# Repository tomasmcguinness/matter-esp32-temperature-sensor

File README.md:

# matter-esp32-temperature-sensor
A simple Matter enabled NTC temperature sensor for ESP32

> [!CAUTION]
> The PCB design has some issues that need to be resolved.

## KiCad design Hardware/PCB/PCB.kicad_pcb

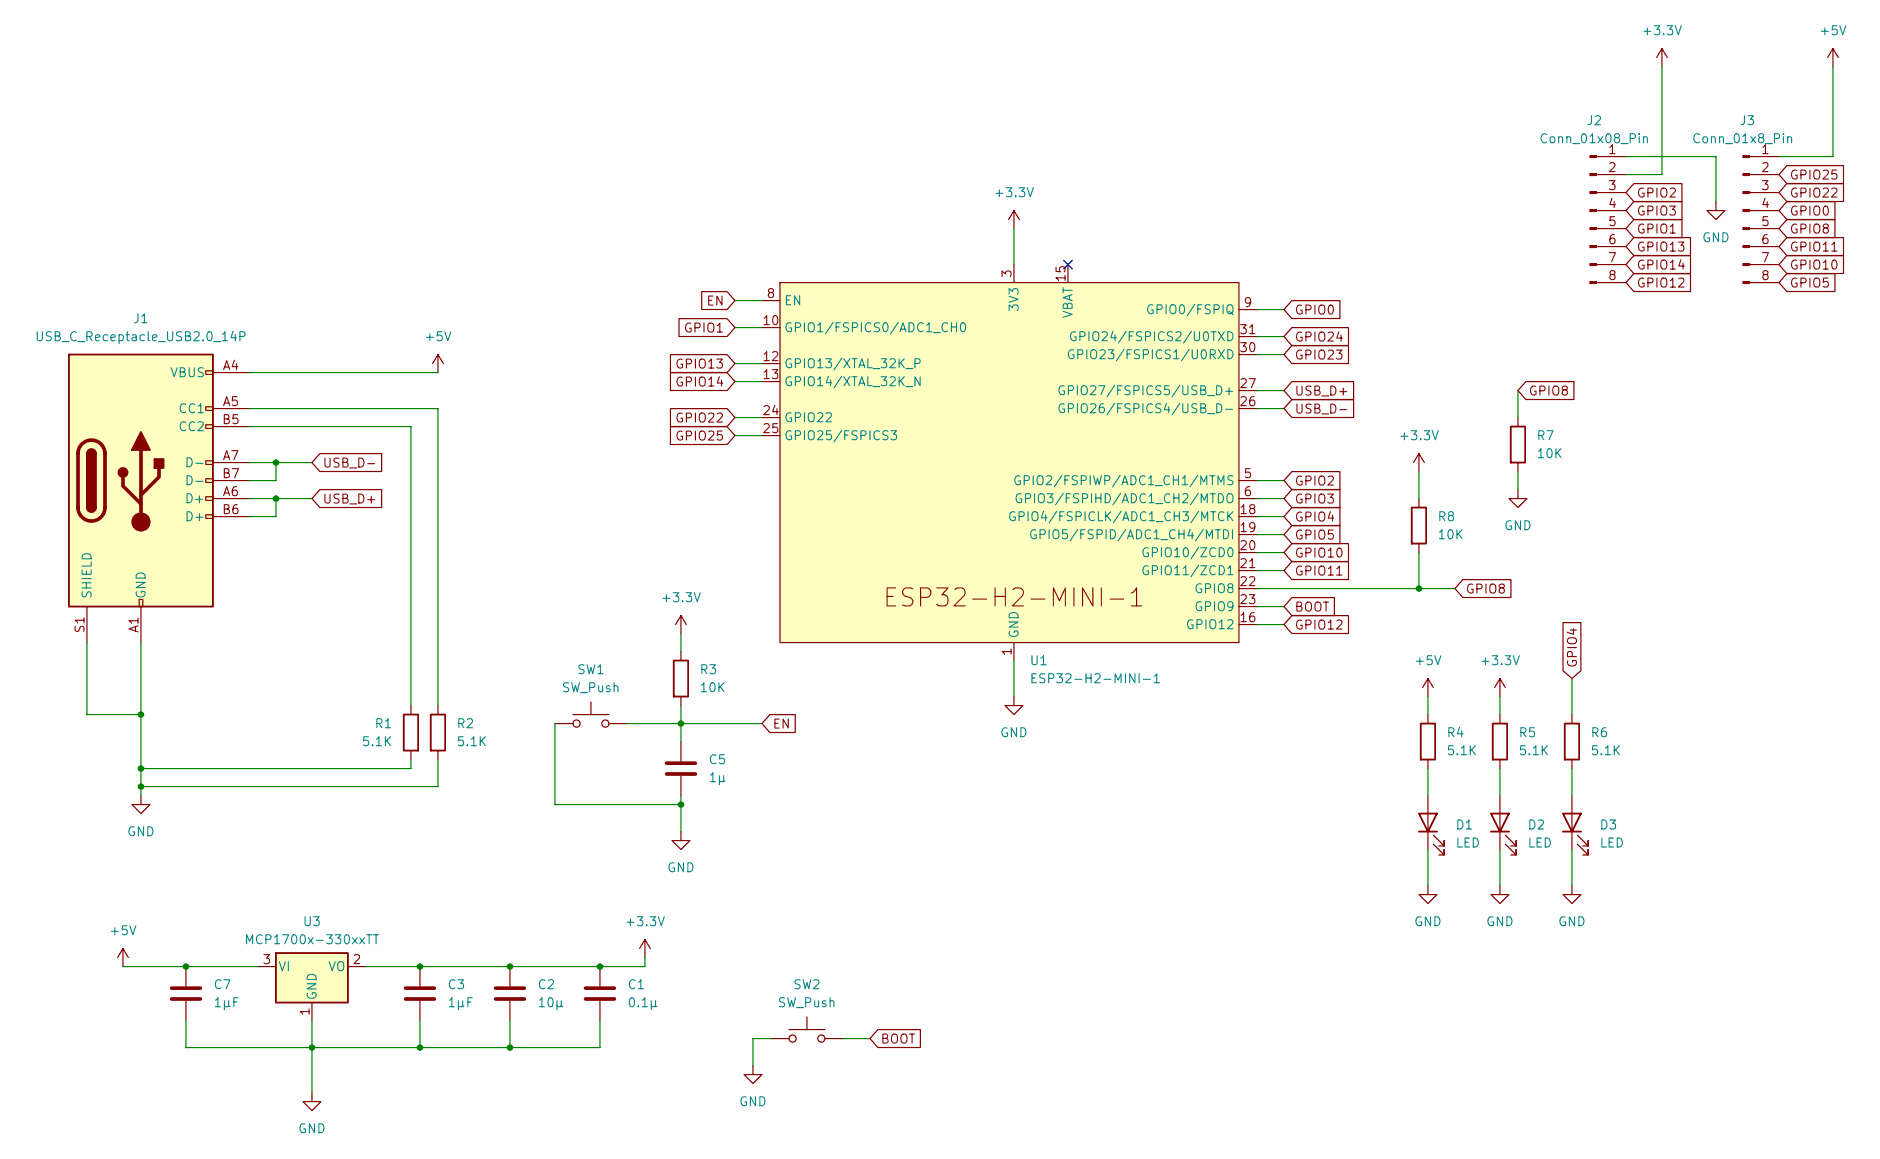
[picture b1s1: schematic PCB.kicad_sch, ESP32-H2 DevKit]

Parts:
C1: 0.1µ; C_0805_2012Metric
C2: 10µ; C_0805_2012Metric
C3, C7: 1µF; C_0805_2012Metric
C5: 1µ; C_0805_2012Metric
D1, D2, D3: LED; LED_0805_2012Metric
J1: USB_C_Receptacle_USB2.0_14P; USB_C_Receptacle_GCT_USB4105-xx-A_16P_TopMnt_Horizontal
J2: Conn_01x08_Pin; PinHeader_1x08_P2.54mm_Vertical
J3: Conn_01x8_Pin; PinHeader_1x08_P2.54mm_Vertical
R1, R2, R4, R5, R6: 5.1K; R_0805_2012Metric
R3, R7, R8: 10K; R_0805_2012Metric
SW1, SW2: SW_Push; SW_SPST_TS-1088-xR025
U1: ESP32-H2-MINI-1
U3: MCP1700x-330xxTT; SOT-23

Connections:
+3.3V: C1.1, C2.1, C3.1, J2.2, R3.1, R5.1, R8.1, U1.3 (3V3), U3.2 (VO)
+5V: C7.1, J1.A4 (VBUS), J1.A9 (VBUS), J1.B4 (VBUS), J1.B9 (VBUS), J3.1, R4.1, U3.3 (VI)
BOOT: SW2.2, U1.23 (GPIO9)
EN: C5.1, R3.2, SW1.2, U1.8 (EN)
GND: C1.2, C2.2, C3.2, C5.2, C7.2, D1.1 (K), D2.1 (K), D3.1 (K), J1.A1 (GND), J1.A12 (GND), J1.B1 (GND), J1.B12 (GND), J1.S1 (SHIELD), J2.1, R1.2, R2.2, R7.2, SW1.1, SW2.1, U1.1 (GND), U1.2 (GND), U1.11 (GND), U1.14 (GND), U1.36 (GND), U1.37 (GND), U1.38 (GND), U1.39 (GND), U1.40 (GND), U1.41 (GND), U1.42 (GND), U1.43 (GND), U1.44 (GND), U1.45 (GND), U1.46 (GND), U1.47 (GND), U1.48 (GND), U1.49 (GND), U1.50 (GND), U1.51 (GND), U1.52 (GND), U1.53 (GND), U3.1 (GND)
GPIO0: J3.4, U1.9 (GPIO0/FSPIQ)
GPIO1: J2.5, U1.10 (GPIO1/FSPICS0/ADC1_CH0)
GPIO2: J2.3, U1.5 (GPIO2/FSPIWP/ADC1_CH1/MTMS)
GPIO3: J2.4, U1.6 (GPIO3/FSPIHD/ADC1_CH2/MTDO)
GPIO4: R6.1, U1.18 (GPIO4/FSPICLK/ADC1_CH3/MTCK)
GPIO5: J3.8, U1.19 (GPIO5/FSPID/ADC1_CH4/MTDI)
GPIO8: J3.5, R7.1, R8.2, U1.22 (GPIO8)
GPIO10: J3.7, U1.20 (GPIO10/ZCD0)
GPIO11: J3.6, U1.21 (GPIO11/ZCD1)
GPIO12: J2.8, U1.16 (GPIO12)
GPIO13: J2.6, U1.12 (GPIO13/XTAL_32K_P)
GPIO14: J2.7, U1.13 (GPIO14/XTAL_32K_N)
GPIO22: J3.3, U1.24 (GPIO22)
GPIO23: U1.30 (GPIO23/FSPICS1/U0RXD)
GPIO24: U1.31 (GPIO24/FSPICS2/U0TXD)
GPIO25: J3.2, U1.25 (GPIO25/FSPICS3)
unnamed: D1.2 (A), R4.2
unnamed: D2.2 (A), R5.2
unnamed: D3.2 (A), R6.2
unnamed: J1.A5 (CC1), R2.1
unnamed: J1.B5 (CC2), R1.1
USB_D+: J1.A6 (D+), J1.B6 (D+), U1.27 (GPIO27/FSPICS5/USB_D+)
USB_D-: J1.A7 (D-), J1.B7 (D-), U1.26 (GPIO26/FSPICS4/USB_D-)

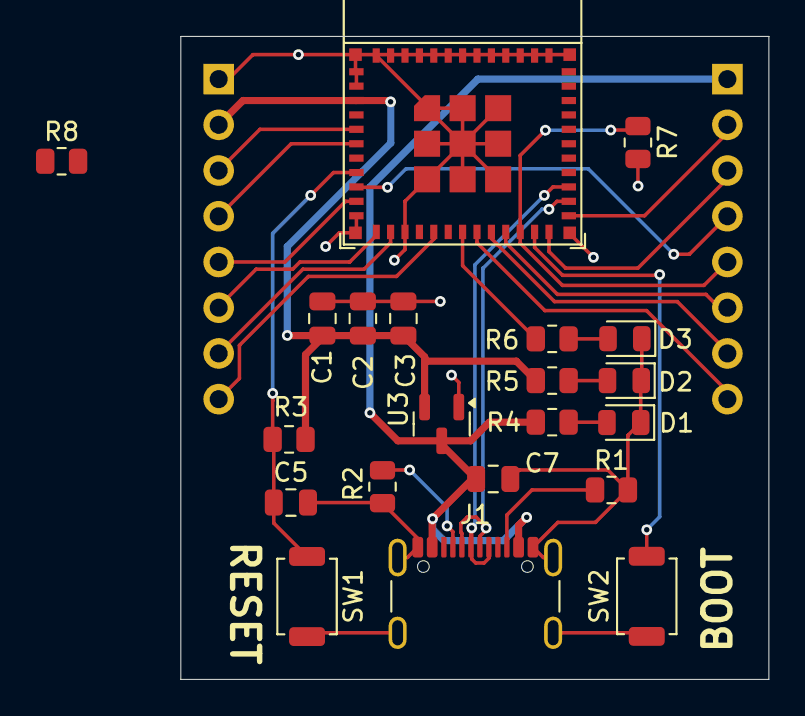
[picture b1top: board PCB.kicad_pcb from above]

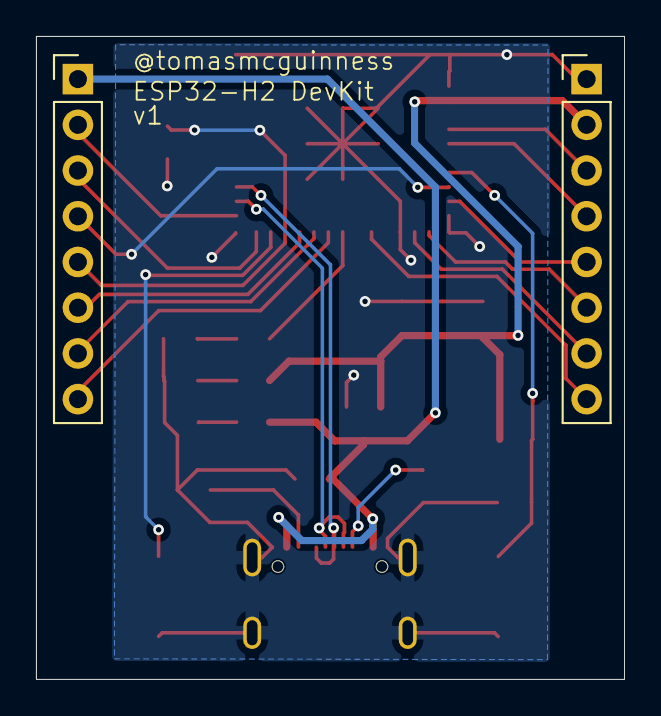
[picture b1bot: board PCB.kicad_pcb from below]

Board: 2 copper layers, 32.7 x 35.7 mm, 23 parts (2 on the bottom side), 26 nets.

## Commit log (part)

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2026-03-08 Initial version with ADC reading on ADC1 Channel 0
2026-03-08 Steinhard calculation added
2026-03-08 Write temperature to MeasuredValue cluster
2026-03-09 Change B Coefficient
2026-03-10 Add near empty KiCad
2026-03-10 Playing with LDOs
2026-03-13 First pass at full layout
2026-03-13 Finished PCB layout
2026-03-13 Fixed up RC capacitor order
2026-03-26 Tweak the Beta Coefficient values and gives better names to things
